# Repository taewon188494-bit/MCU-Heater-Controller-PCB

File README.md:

# MCU Heater Controller PCB

NTC 온도센서 피드백을 기반으로 MCU가 히터를 제어하도록 설계한
2-layer PCB 프로젝트입니다.

MCU의 PWM 신호로 N-channel MOSFET을 구동하여 5 V 히터를 제어하고,
NTC 센서의 아날로그 출력 전압을 MCU ADC로 전달하도록
Schematic 및 PCB Layout을 설계했습니다.

## System Overview

- Heater Supply: 5 V
- Heater Load: 10 Ω
- Calculated Heater Current: 0.5 A
- MCU Logic Level: 3.3 V
- Heater Switching: N-channel MOSFET
- Temperature Sensing: NTC voltage-divider based ADC input
- PCB: 2-layer
- Design Tool: KiCad

## Schematic

회로는 **전원부, 히터 구동부, 온도 센싱부, MCU 인터페이스**로 구성했습니다.

- 5 V 입력으로부터 3.3 V 전원 생성
- MCU_PWM 신호를 이용한 MOSFET gate 제어
- N-channel MOSFET을 이용한 heater low-side switching
- NTC 센서 신호를 TEMP_ADC로 전달
- MOSFET gate resistor 및 pull-down resistor 적용
- 전원 안정화를 위한 decoupling capacitor 적용

## PCB Layout

PCB Layout에서는 히터 스위칭부와 온도 센싱부 사이의 간섭 가능성을 줄이고,
전원 및 신호 경로를 단순화하는 방향으로 부품을 배치하고 배선했습니다.

주요 Layout 고려사항은 다음과 같습니다.

- HEATER_SW 전류 경로 최소화
- MOSFET과 heater connector 간 배선 최소화
- MCU_PWM과 TEMP_ADC 신호 경로 분리
- Switching section과 sensor section 간 물리적 거리 확보
- Ground return path를 고려한 부품 배치
- 2-layer PCB를 활용한 routing 구성

실제 노이즈 계측이나 SI/EMI 해석을 수행한 것은 아니며,
스위칭 회로와 아날로그 센싱 회로의 특성을 고려하여
배치 및 배선 단계에서 간섭 가능성을 줄이는 방향으로 설계했습니다.

## 3D View

PCB Layout 완료 후 KiCad 3D Viewer를 이용하여

- 부품 배치
- Connector 방향
- Board outline
- 기본적인 부품 간 배치 간섭 여부

를 확인했습니다.

## Design Process

1. Heater 및 NTC sensor 요구사항 정의
2. Datasheet 기반 MOSFET 및 주요 부품 선정
3. Schematic 작성 및 회로 연결 검토
4. Footprint 설정 및 PCB 부품 배치
5. Power / sensor signal routing
6. Ground return path 및 switching noise 가능성을 고려한 Layout 검토
7. 3D View를 이용한 최종 배치 및 형상 확인

## Design Considerations

### MOSFET Switching

3.3 V MCU PWM 신호로 5 V heater load를 제어하기 위해
N-channel MOSFET 기반 low-side switching 구조를 적용했습니다.

Gate 입력에는 resistor와 pull-down resistor를 구성하여
MCU 출력과 MOSFET gate 사이의 인터페이스를 구성했습니다.

### Temperature Sensing

NTC 센서의 저항 변화를 전압으로 변환하여
MCU ADC에서 읽을 수 있도록 voltage-divider 기반 센싱 회로를 구성했습니다.

TEMP_ADC 신호가 heater switching node와 불필요하게 인접하지 않도록
PCB 배치와 routing을 검토했습니다.

### Power and Signal Separation

Heater switching path와 temperature sensing path의 역할이 다르다고 판단하여
PCB 상에서 전력부와 센서부를 가능한 한 분리하여 배치했습니다.

특히 HEATER_SW 경로는 짧게 구성하고,
MCU_PWM 및 TEMP_ADC 신호가 서로 불필요하게 교차하지 않도록 routing했습니다.

## Design Files

- `Heater_Controller.kicad_pro`
- `Heater_Controller.kicad_sch`
- `Heater_Controller.kicad_pcb`

KiCad에서 직접 열어 Schematic과 PCB Layout을 확인할 수 있습니다.

## Project Status

완료한 범위:

- Schematic 설계
- Datasheet 기반 주요 부품 선정
- Footprint 설정
- PCB 부품 배치
- 2-layer Routing
- Ground 및 signal routing 검토
- 3D View를 통한 배치 확인

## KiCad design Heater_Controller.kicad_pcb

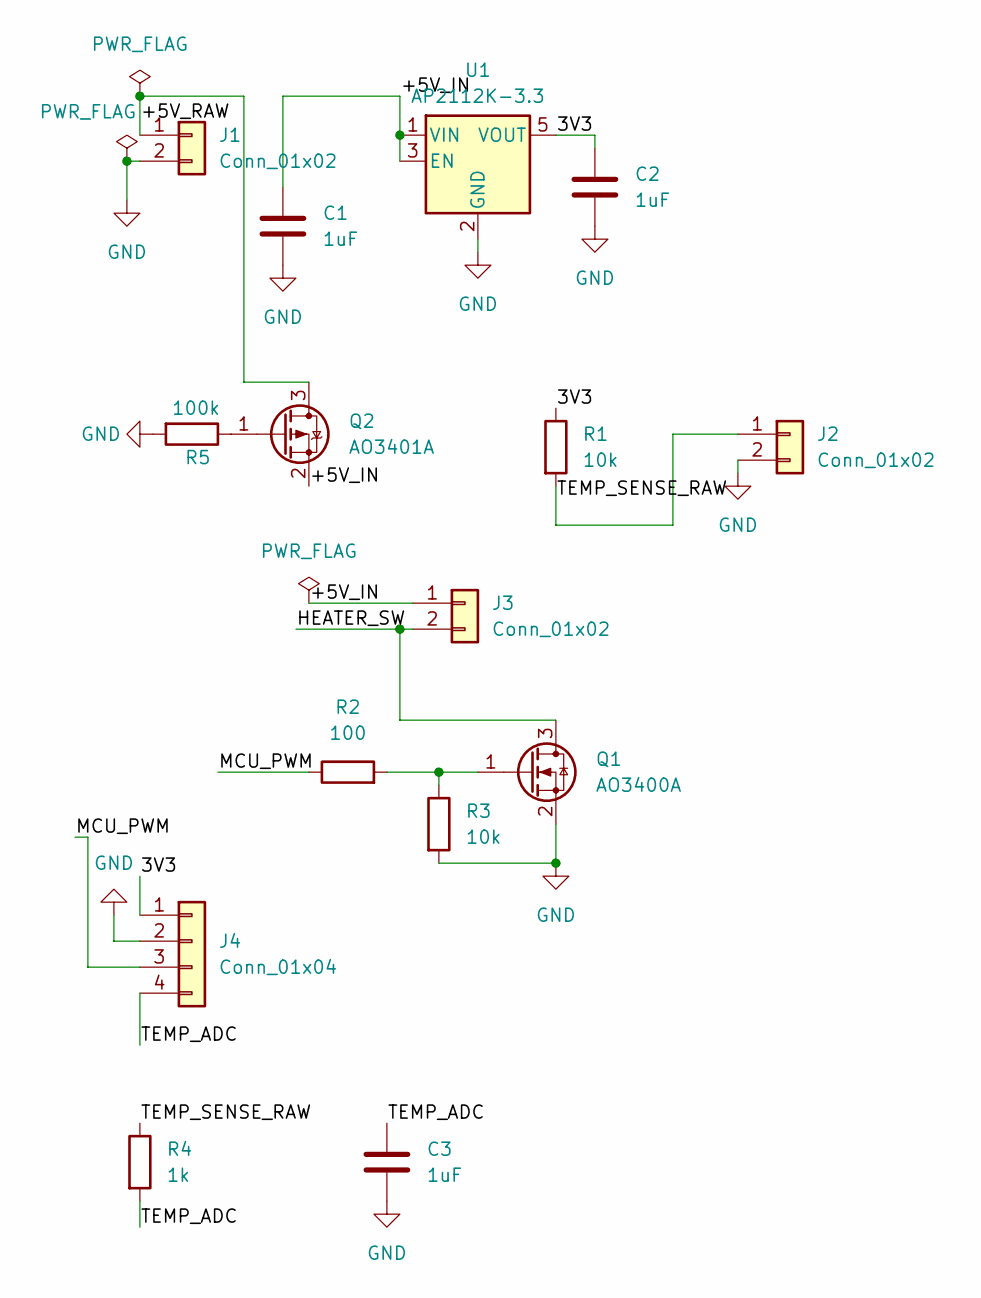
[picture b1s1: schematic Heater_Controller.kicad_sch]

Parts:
C1, C2, C3: 1uF; C_0805_2012Metric
J1, J2, J3: Conn_01x02; PinHeader_1x02_P2.54mm_Vertical
J4: Conn_01x04; PinHeader_1x04_P2.54mm_Vertical
Q1: AO3400A; SOT-23
Q2: AO3401A; SOT-23
R1, R3: 10k; R_0805_2012Metric
R2: 100; R_0805_2012Metric
R4: 1k; R_0805_2012Metric
R5: 100k; R_0805_2012Metric
U1: AP2112K-3.3; SOT-23-5

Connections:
/3V3: C2.1, J4.1, R1.1, U1.5 (VOUT)
/+5V_IN: C1.1, J3.1, Q2.2 (S), U1.1 (VIN), U1.3 (EN)
/+5V_RAW: J1.1, Q2.3 (D)
/HEATER_SW: J3.2, Q1.3 (D)
/MCU_PWM: J4.3, R2.1
/TEMP_ADC: C3.1, J4.4, R4.2
/TEMP_SENSE_RAW: J2.1, R1.2, R4.1
GND: C1.2, C2.2, C3.2, J1.2, J2.2, J4.2, Q1.2 (S), R3.2, R5.2, U1.2 (GND)
unnamed: Q1.1 (G), R2.2, R3.1
unnamed: Q2.1 (G), R5.1

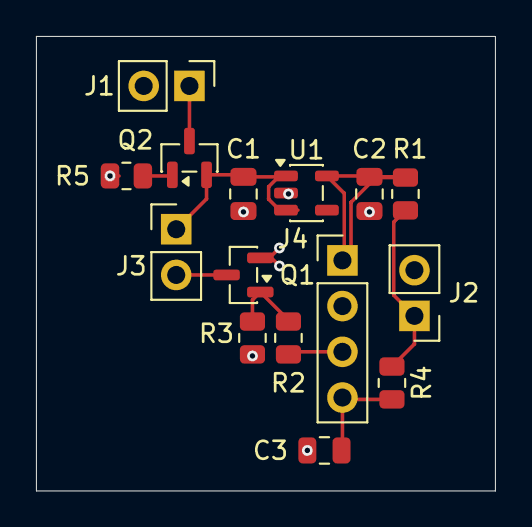
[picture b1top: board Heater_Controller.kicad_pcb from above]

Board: 2 copper layers, 25.5 x 25.2 mm, 15 parts (0 on the bottom side), 10 nets.
